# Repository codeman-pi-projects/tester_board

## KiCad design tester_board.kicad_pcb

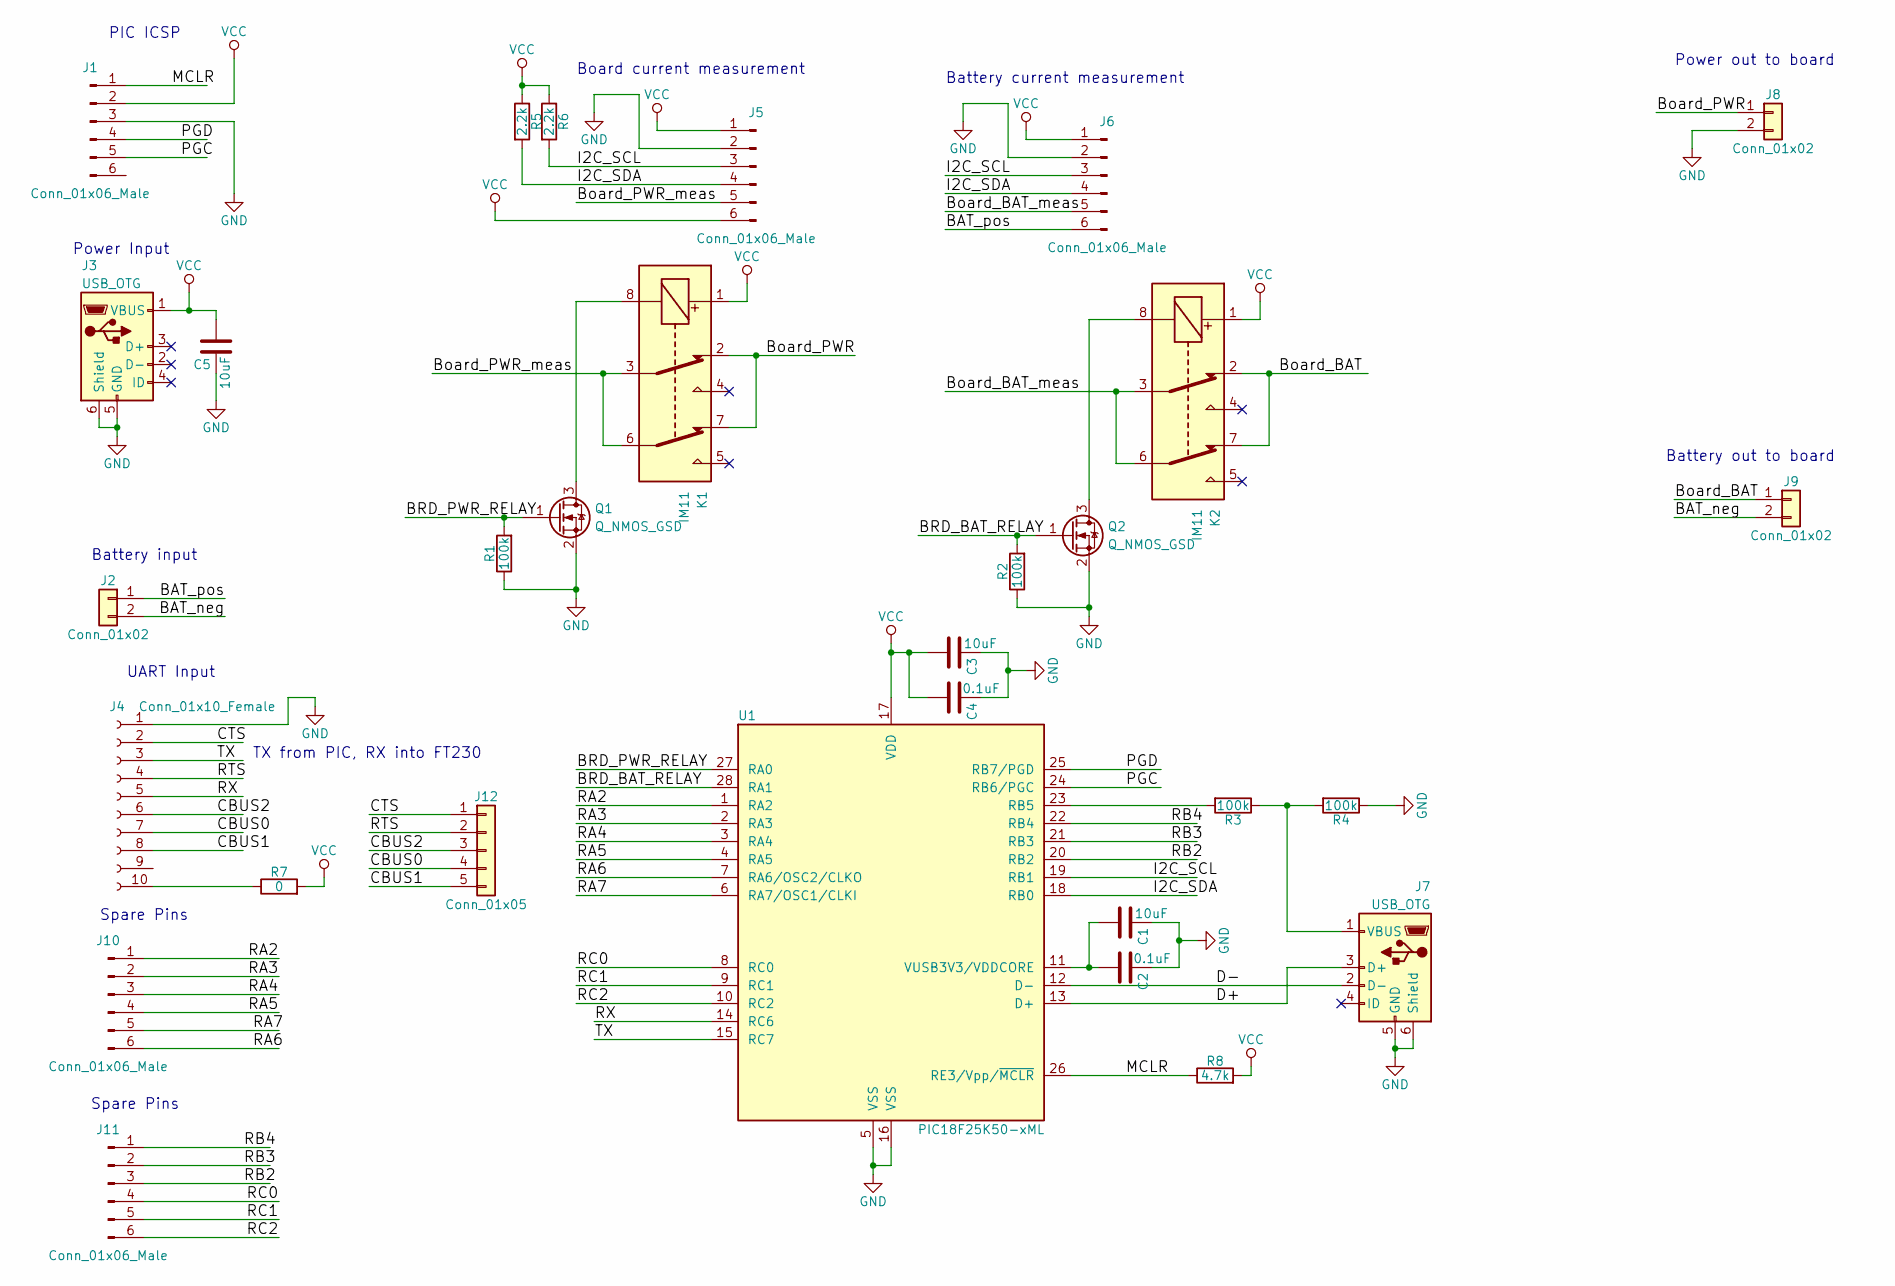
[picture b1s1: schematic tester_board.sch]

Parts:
C1, C3, C5: 10uF; C_0805
C2, C4: 0.1uF; C_0603
J1: Conn_01x06_Male; Pin_Header_Angled_1x06_Pitch2.54mm
J2, J8, J9: Conn_01x02; Pin_Header_Straight_1x02_Pitch2.54mm
J3, J7: USB_OTG; USB_Micro-B_Molex_47346-0001
J4: Conn_01x10_Female; Socket_Strip_Straight_1x10_Pitch2.54mm
J5, J6, J10, J11: Conn_01x06_Male; Pin_Header_Straight_1x06_Pitch2.54mm
J12: Conn_01x05; Socket_Strip_Straight_1x05_Pitch2.54mm
K1, K2: IM11; Relay_DPDT_AXICOM_IMSeries_Pitch3.2mm
Q1, Q2: Q_NMOS_GSD; SOT-23
R1, R2, R3, R4: 100k; R_0603
R5, R6: 2.2k; R_0603
R7: 0; R_0603
R8: 4.7k; R_0603
U1: PIC18F25K50-xML; QFN-28-1EP_6x6mm_Pitch0.65mm

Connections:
/BAT_neg: J2.2, J9.2
/BAT_pos: J2.1, J6.6
/BRD_BAT_RELAY: Q2.1 (G), R2.2, U1.28 (RA1)
/BRD_PWR_RELAY: Q1.1 (G), R1.2, U1.27 (RA0)
/Board_BAT: J9.1, K2.2, K2.7
/Board_BAT_meas: J6.5, K2.3, K2.6
/Board_PWR: J8.1, K1.2, K1.7
/Board_PWR_meas: J5.5, K1.3, K1.6
/CBUS0: J4.7, J12.4
/CBUS1: J4.8, J12.5
/CBUS2: J4.6, J12.3
/CTS: J4.2, J12.1
/D+: J7.3 (D+), U1.13 (D+)
/D-: J7.2 (D-), U1.12 (D-)
/I2C_SCL: J5.3, J6.3, R6.2, U1.19 (RB1)
/I2C_SDA: J5.4, J6.4, R5.2, U1.18 (RB0)
/MCLR: J1.1, R8.1, U1.26 (RE3/Vpp/~MCLR~)
/PGC: J1.5, U1.24 (RB6/PGC)
/PGD: J1.4, U1.25 (RB7/PGD)
/RA2: J10.1, U1.1 (RA2)
/RA3: J10.2, U1.2 (RA3)
/RA4: J10.3, U1.3 (RA4)
/RA5: J10.4, U1.4 (RA5)
/RA6: J10.6, U1.7 (RA6/OSC2/CLKO)
/RA7: J10.5, U1.6 (RA7/OSC1/CLKI)
/RB2: J11.3, U1.20 (RB2)
/RB3: J11.2, U1.21 (RB3)
/RB4: J11.1, U1.22 (RB4)
/RC0: J11.4, U1.8 (RC0)
/RC1: J11.5, U1.9 (RC1)
/RC2: J11.6, U1.10 (RC2)
/RTS: J4.4, J12.2
/RX: J4.5, U1.14 (RC6)
/TX: J4.3, U1.15 (RC7)
GND: C1.1, C2.1, C3.1, C4.1, C5.1, J1.3, J3.5 (GND), J3.6 (Shield), J4.1, J5.2, J6.2, J7.5 (GND), J7.6 (Shield), J8.2, Q1.2 (S), Q2.2 (S), R1.1, R2.1, R4.1, U1.5 (VSS), U1.16 (VSS)
unnamed: C1.2, C2.2, U1.11 (VUSB3V3/VDDCORE)
unnamed: J4.10, R7.1
unnamed: J7.1 (VBUS), R3.1, R4.2
unnamed: K1.8, Q1.3 (D)
unnamed: K2.8, Q2.3 (D)
unnamed: R3.2, U1.23 (RB5)
VCC: C3.2, C4.2, C5.2, J1.2, J3.1 (VBUS), J5.1, J5.6, J6.1, K1.1, K2.1, R5.1, R6.1, R7.2, R8.2, U1.17 (VDD)

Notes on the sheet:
PIC ICSP
Power Input
Board current measurement
Power out to board
Battery current measurement
Battery out to board
Battery input
UART Input
Spare Pins
TX from PIC, RX into FT230

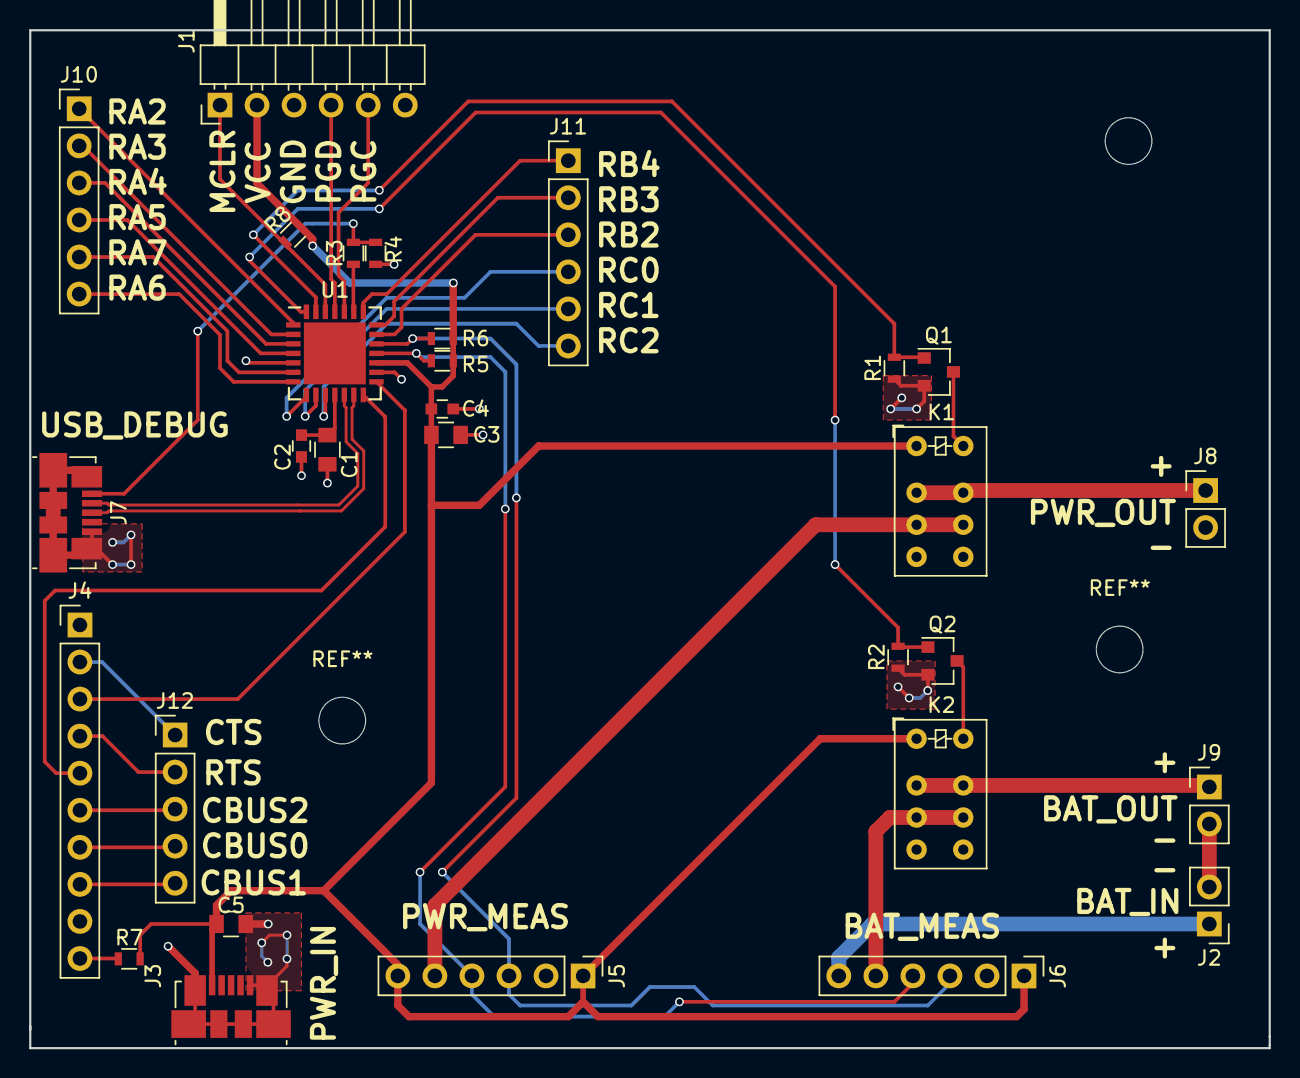
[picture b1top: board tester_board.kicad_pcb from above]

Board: 2 copper layers, 85.0 x 69.8 mm, 30 parts (0 on the bottom side), 42 nets.

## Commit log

2018-07-06 USB diff pair routed
2018-08-24 finished
